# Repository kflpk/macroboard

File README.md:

# Macroboard

Simple ortholinear 4x4 macro keyboard with rotary encoder.

## Schematics

The schematics and PCB were created using KiCAD 7. The microcontroller used is an STM32F103C6T6.

## PCB
Front | Back
:-------------------------:|:-------------------------:
 | 

## Mechanical parts

Mechanical design was done using Fusion 360. The front plate is a 1.5 mm thick aluminium plate, cut using a 3-axis CNC machine.
Standoffs for the board and plate were 3D printed with TPU.

You can find all the necessary files in the "mechanical" folder.

## Dependencies
```
arm-none-eabi-binutils
arm-none-eabi-gcc
arm-none-eabi-newlib
```

## Authors
* Kacper Filipek
* Krzysztof Sikora

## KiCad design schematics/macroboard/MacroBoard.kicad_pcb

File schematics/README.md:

# macroboard
Simple macro keyboard for computers

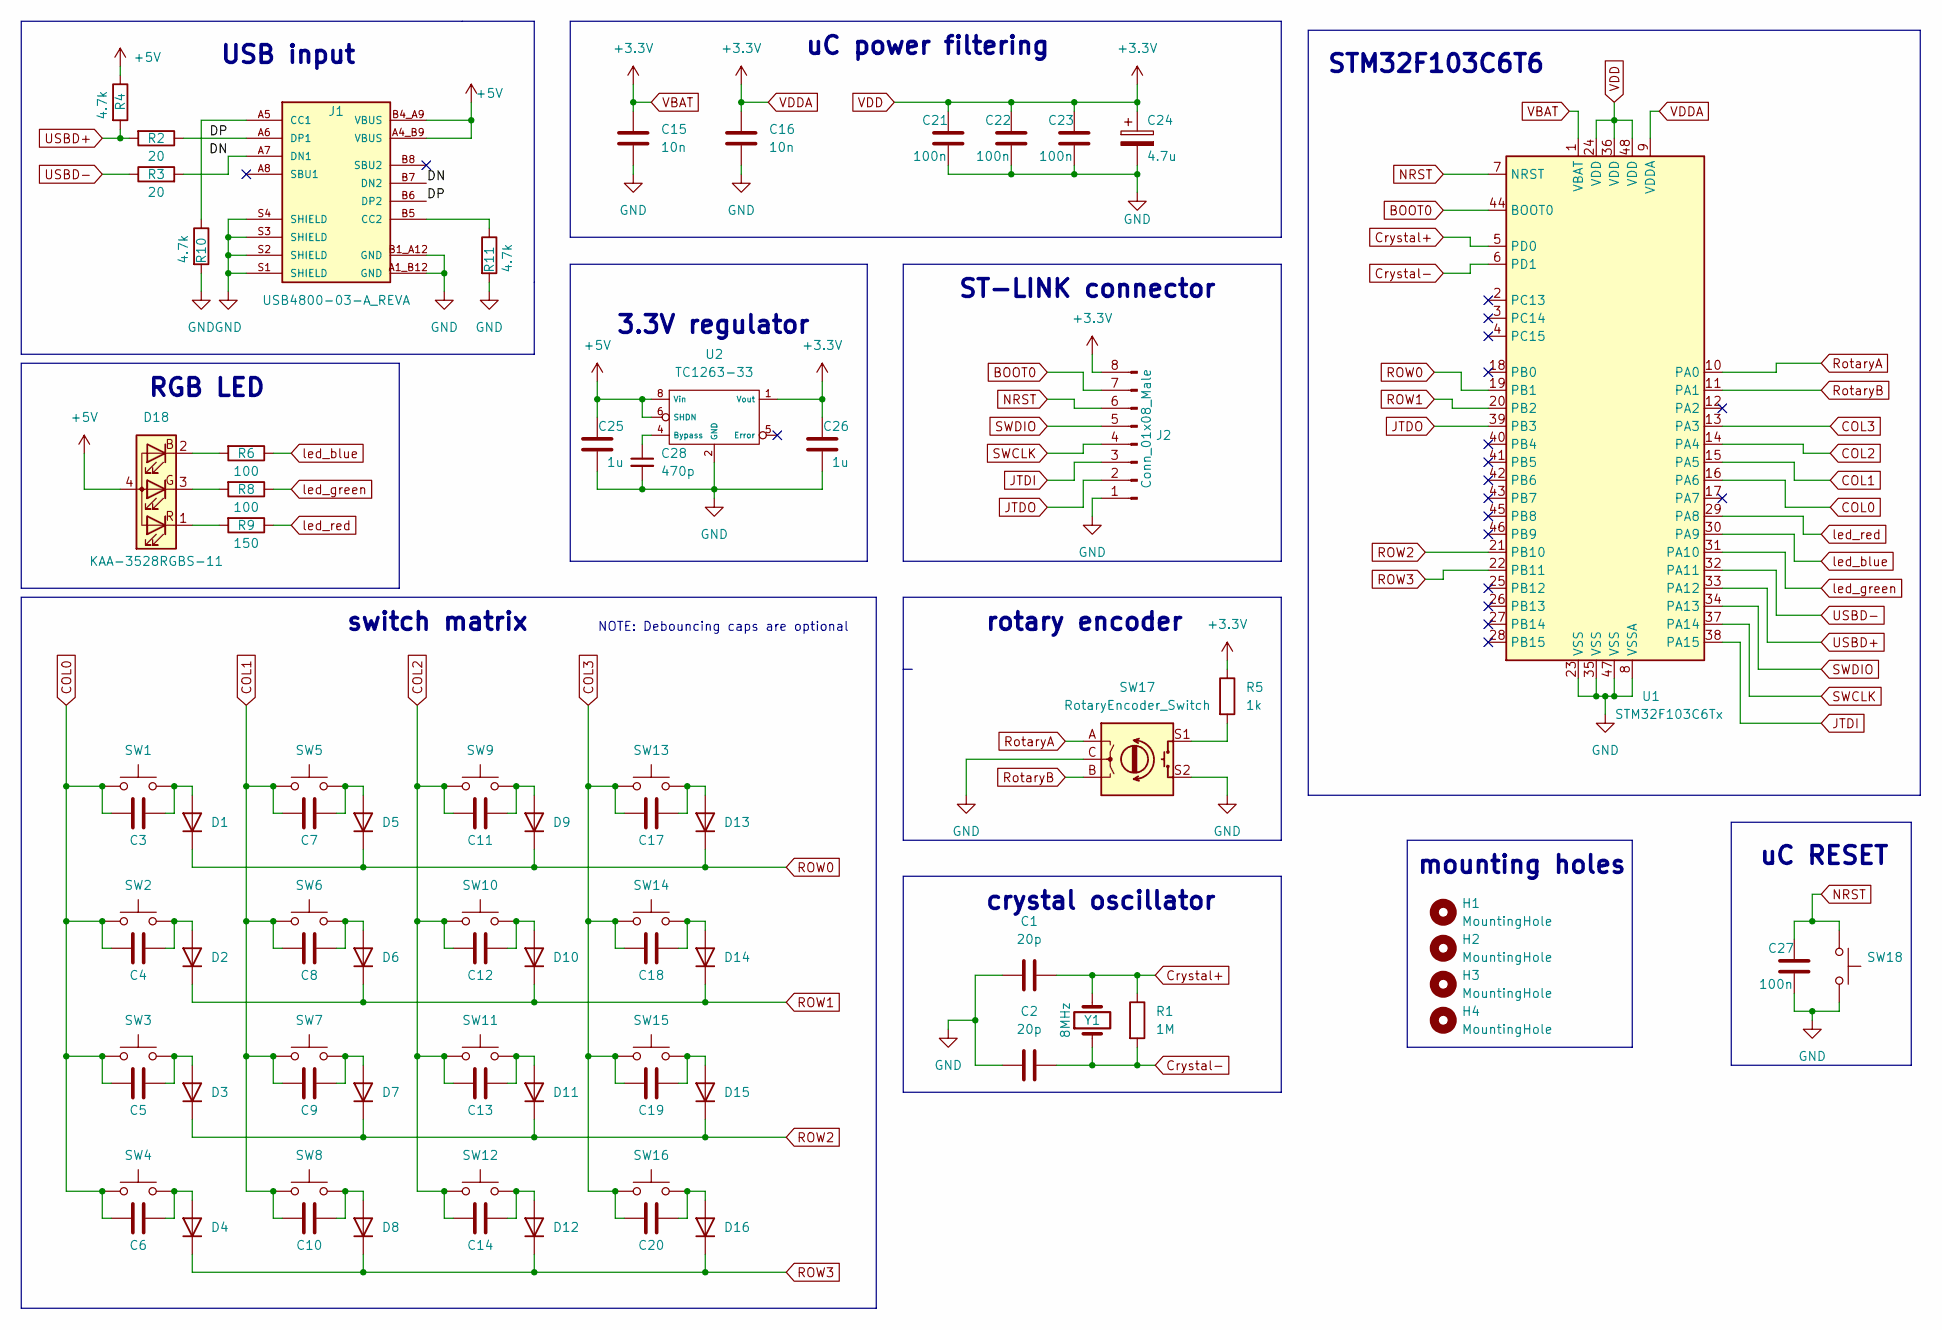
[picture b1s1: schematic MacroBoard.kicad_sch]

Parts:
C1, C2: 20p; C_0603_1608Metric_Pad1.08x0.95mm_HandSolder
C3, C4, C5, C6, C7, C8, C9, C10, C11, C12, C13, C14, C17, C18, C19, C20: C; C_0805_2012Metric_Pad1.18x1.45mm_HandSolder
C15, C16: 10n; C_0805_2012Metric_Pad1.18x1.45mm_HandSolder
C21, C22, C23, C27: 100n; C_0805_2012Metric_Pad1.18x1.45mm_HandSolder
C24: 4.7u; C_0805_2012Metric_Pad1.18x1.45mm_HandSolder
C25, C26: 1u; C_0805_2012Metric_Pad1.18x1.45mm_HandSolder
C28: 470p; C_0805_2012Metric_Pad1.18x1.45mm_HandSolder
D1, D2, D3, D4, D5, D6, D7, D8, D9, D10, D11, D12, D13, D14, D15, D16: D; D_SOD-123F
D18: KAA-3528RGBS-11; LED_AAA3528LSEKJ3ZGKQBKS
H1, H2, H3, H4: MountingHole; MountingHole_3mm
J1: USB4800-03-A_REVA; GCT_USB4800-03-A_REVA; PARTREV A
J2: Conn_01x08_Male; PinHeader_1x08_P2.54mm_Horizontal
R1: 1M; R_1206_3216Metric_Pad1.30x1.75mm_HandSolder
R2, R3: 20; R_1206_3216Metric_Pad1.30x1.75mm_HandSolder
R4, R10, R11: 4.7k; R_1206_3216Metric_Pad1.30x1.75mm_HandSolder
R5: 1k; R_1206_3216Metric_Pad1.30x1.75mm_HandSolder
R6, R8: 100; R_1206_3216Metric_Pad1.30x1.75mm_HandSolder
R9: 150; R_1206_3216Metric_Pad1.30x1.75mm_HandSolder
SW1, SW2, SW3, SW4, SW5, SW6, SW7, SW8, SW9, SW10, SW11, SW12, SW13, SW14, SW15, SW16: SW_Push; SW_Cherry_MX_1.00u_PCB
SW17: RotaryEncoder_Switch; RotaryEncoder_Alps_EC11E-Switch_Vertical_H20mm
SW18: SW_Push; SW_SPST_TL3342
U1: STM32F103C6Tx; LQFP-48_7x7mm_P0.5mm
U2: TC1263-33; PowerIntegrations_SO-8
Y1: 8MHz; Crystal_SMD_HC49-SD

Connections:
+5V: C25.1, D18.4 (A), J1.A4_B9 (VBUS), J1.B4_A9 (VBUS), R4.1, U2.6 (SHDN), U2.8 (Vin)
/DN: J1.A7 (DN1), J1.B7 (DN2), R3.2
/DP: J1.A6 (DP1), J1.B6 (DP2), R2.1
BOOT0: J2.7, U1.44 (BOOT0)
COL0: C3.1, C4.1, C5.1, C6.1, SW1.1, SW2.1, SW3.1, SW4.1, U1.16 (PA6)
COL1: C7.1, C8.1, C9.1, C10.1, SW5.1, SW6.1, SW7.1, SW8.1, U1.15 (PA5)
COL2: C11.1, C12.1, C13.1, C14.1, SW9.1, SW10.1, SW11.1, SW12.1, U1.14 (PA4)
COL3: C17.1, C18.1, C19.1, C20.1, SW13.1, SW14.1, SW15.1, SW16.1, U1.13 (PA3)
Crystal+: C1.2, R1.1, U1.5 (PD0), Y1.2
Crystal-: C2.2, R1.2, U1.6 (PD1), Y1.1
GND: C1.1, C2.1, C15.2, C16.2, C21.2, C22.2, C23.2, C24.2, C25.2, C26.2, C27.1, C28.2, J1.A1_B12 (GND), J1.B1_A12 (GND), J1.S1 (SHIELD), J1.S2 (SHIELD), J1.S3 (SHIELD), J1.S4 (SHIELD), J2.1, R10.2, R11.2, SW17.C, SW17.S2, SW18.2, U1.8 (VSSA), U1.23 (VSS), U1.35 (VSS), U1.47 (VSS), U2.2 (GND)
JTDI: J2.3, U1.38 (PA15)
JTDO: J2.2, U1.39 (PB3)
NRST: C27.2, J2.6, SW18.1, U1.7 (NRST)
unnamed: C3.2, D1.2 (A), SW1.2
unnamed: C4.2, D2.2 (A), SW2.2
unnamed: C5.2, D3.2 (A), SW3.2
unnamed: C6.2, D4.2 (A), SW4.2
unnamed: C7.2, D5.2 (A), SW5.2
unnamed: C8.2, D6.2 (A), SW6.2
unnamed: C9.2, D7.2 (A), SW7.2
unnamed: C10.2, D8.2 (A), SW8.2
unnamed: C11.2, D9.2 (A), SW9.2
unnamed: C12.2, D10.2 (A), SW10.2
unnamed: C13.2, D11.2 (A), SW11.2
unnamed: C14.2, D12.2 (A), SW12.2
unnamed: C17.2, D13.2 (A), SW13.2
unnamed: C18.2, D14.2 (A), SW14.2
unnamed: C19.2, D15.2 (A), SW15.2
unnamed: C20.2, D16.2 (A), SW16.2
unnamed: C28.1, U2.4 (Bypass)
unnamed: D18.1 (RK), R9.2
unnamed: D18.2 (BK), R6.2
unnamed: D18.3 (GK), R8.2
unnamed: J1.A5 (CC1), R10.1
unnamed: J1.B5 (CC2), R11.1
unnamed: R5.2, SW17.S1
ROW0: D1.1 (K), D5.1 (K), D9.1 (K), D13.1 (K), U1.19 (PB1)
ROW1: D2.1 (K), D6.1 (K), D10.1 (K), D14.1 (K), U1.20 (PB2)
ROW2: D3.1 (K), D7.1 (K), D11.1 (K), D15.1 (K), U1.21 (PB10)
ROW3: D4.1 (K), D8.1 (K), D12.1 (K), D16.1 (K), U1.22 (PB11)
RotaryA: SW17.A, U1.10 (PA0)
RotaryB: SW17.B, U1.11 (PA1)
SWCLK: J2.4, U1.37 (PA14)
SWDIO: J2.5, U1.34 (PA13)
USBD+: R2.2, R4.2, U1.33 (PA12)
USBD-: R3.1, U1.32 (PA11)
VBAT: C15.1, C16.1, C21.1, C22.1, C23.1, C24.1, C26.1, J2.8, R5.1, U1.1 (VBAT), U1.9 (VDDA), U1.24 (VDD), U1.36 (VDD), U1.48 (VDD), U2.1 (Vout)
led_blue: R6.1, U1.30 (PA9)
led_green: R8.1, U1.31 (PA10)
led_red: R9.1, U1.29 (PA8)

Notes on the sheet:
STM32F103C6T6
rotary encoder
uC RESET
switch matrix
USB input
mounting holes
3.3V regulator
RGB LED
ST-LINK connector
crystal oscillator
uC power filtering
NOTE: Debouncing caps are optional

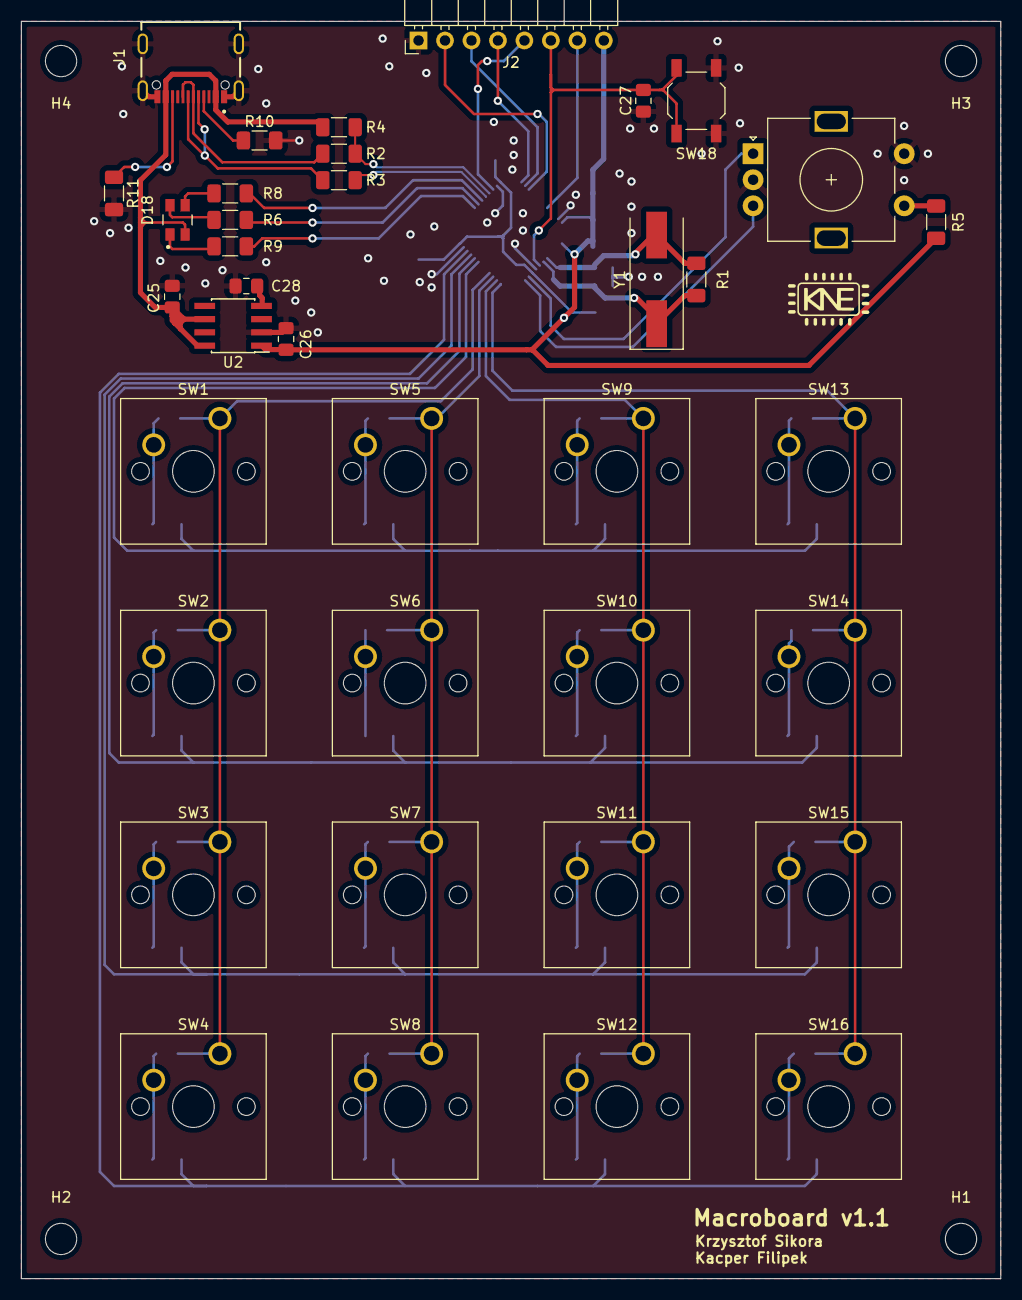
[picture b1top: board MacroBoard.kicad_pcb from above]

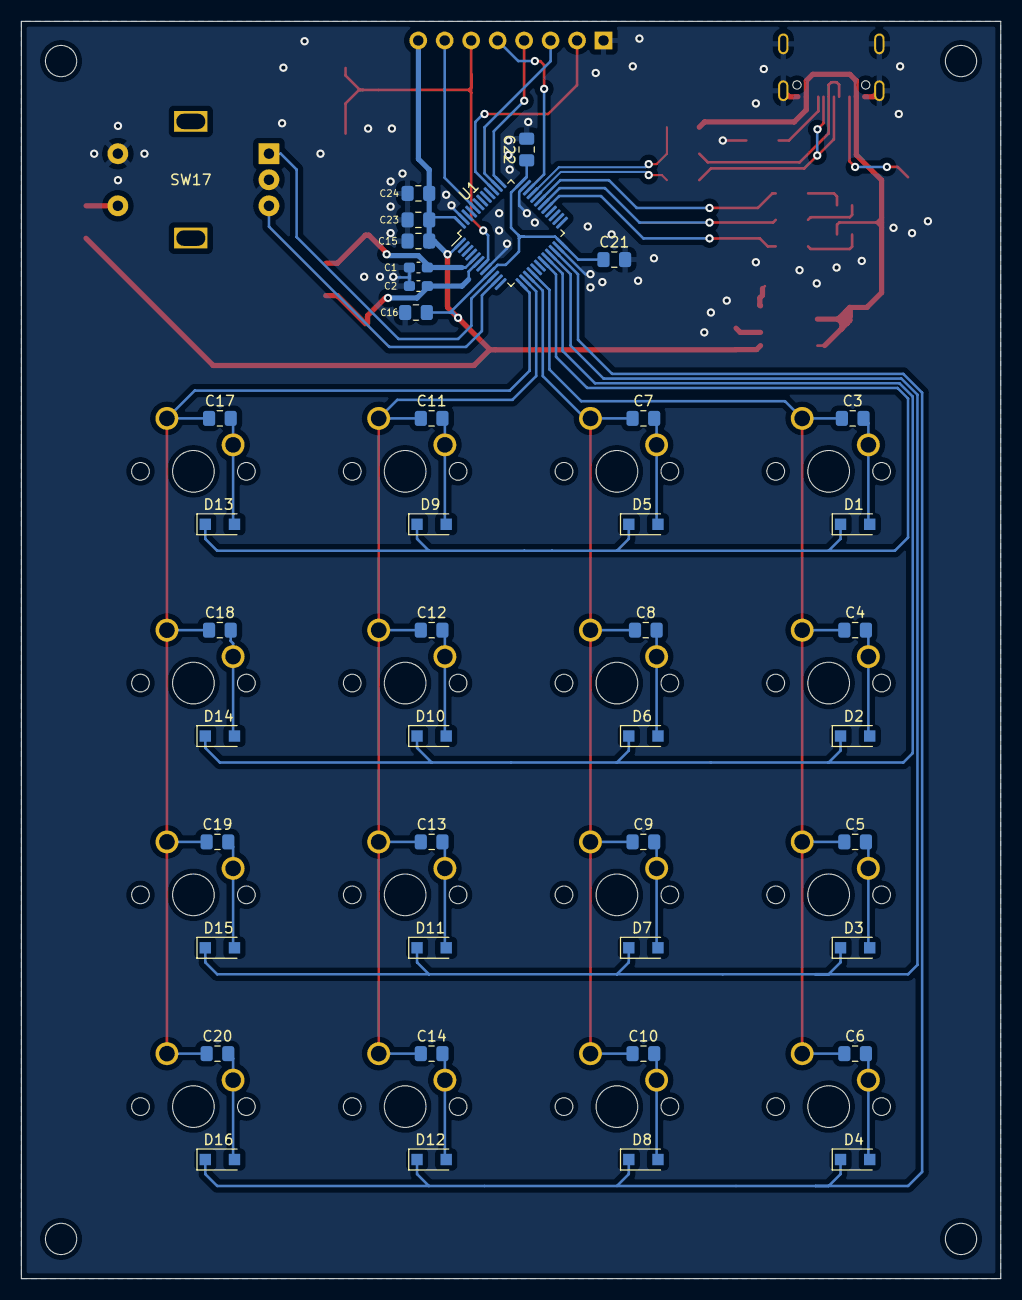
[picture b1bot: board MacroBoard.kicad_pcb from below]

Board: 2 copper layers, 94.0 x 120.6 mm, 82 parts (41 on the bottom side), 51 nets.

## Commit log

2022-12-15 Add files via upload
    TODO:
    add footprints
    add pads for measurments
    create PCB design
2022-12-15 Add files via upload
    Pinout changes
2022-12-18 schematic done
2022-12-18 footprints used in the project
2022-12-20 pcb: arranged and connected switches with caps and diodes, everything else sucks
2022-12-20 connected rows and cols to MCU, gotto re-route it anyway because of the USB connectors being on the bad side
2022-12-22 stuff
2022-12-23 placed all components
2022-12-23 before flipping columns
2022-12-23 flipped columns, connected columns and rows and programming pins in pcb
2022-12-23 i hope it's finished
2022-12-23 signing on silkscreen
2022-12-24 added logo
2023-02-28 removed backups, added to gitignore
2023-02-28 moved kikad files to 'schematics' folder
2023-04-08 moved readme to root
2023-04-08 removed unnecessary libraries from project files
2023-04-11 final pcb updates
2023-04-11 minor cleanup on schematic, hided value labels on switches on keyboard matrix for better readability
2023-05-10 some automatic changes in kicad files
2023-05-10 added basic readme
2023-05-10 minor changes to readme
2023-05-21 minor readme update, added qmk configuration for the keyboard
2023-05-21 minor comments about licensing
2023-05-21 added copyright notice
2023-05-29 schematic: moved row connections to the side of the pcb
2023-08-29 added numpad keymap
2023-08-29 cleanup for keymaps
2023-08-29 deleted LDSCRIPT from rules.mk
2025-04-25 Added mechanical parts and updated README
